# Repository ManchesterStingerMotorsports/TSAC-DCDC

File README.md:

# TSAC-DCDC
Low power HV-LV flyback converter to power the TSAC's internal safety circuitry.

Input voltage:

	Min: 35V to allow for single segment operation
	Max: 600V to allow for use across accumulator types

Estimated Output @ 12V with minimal ripple:

	6W continuous
	24W Peak

Webench design tool link for simulation and specs:
https://webench.ti.com/appinfo/webench/scripts/SDP.cgi?ID=1A791EA787B34855

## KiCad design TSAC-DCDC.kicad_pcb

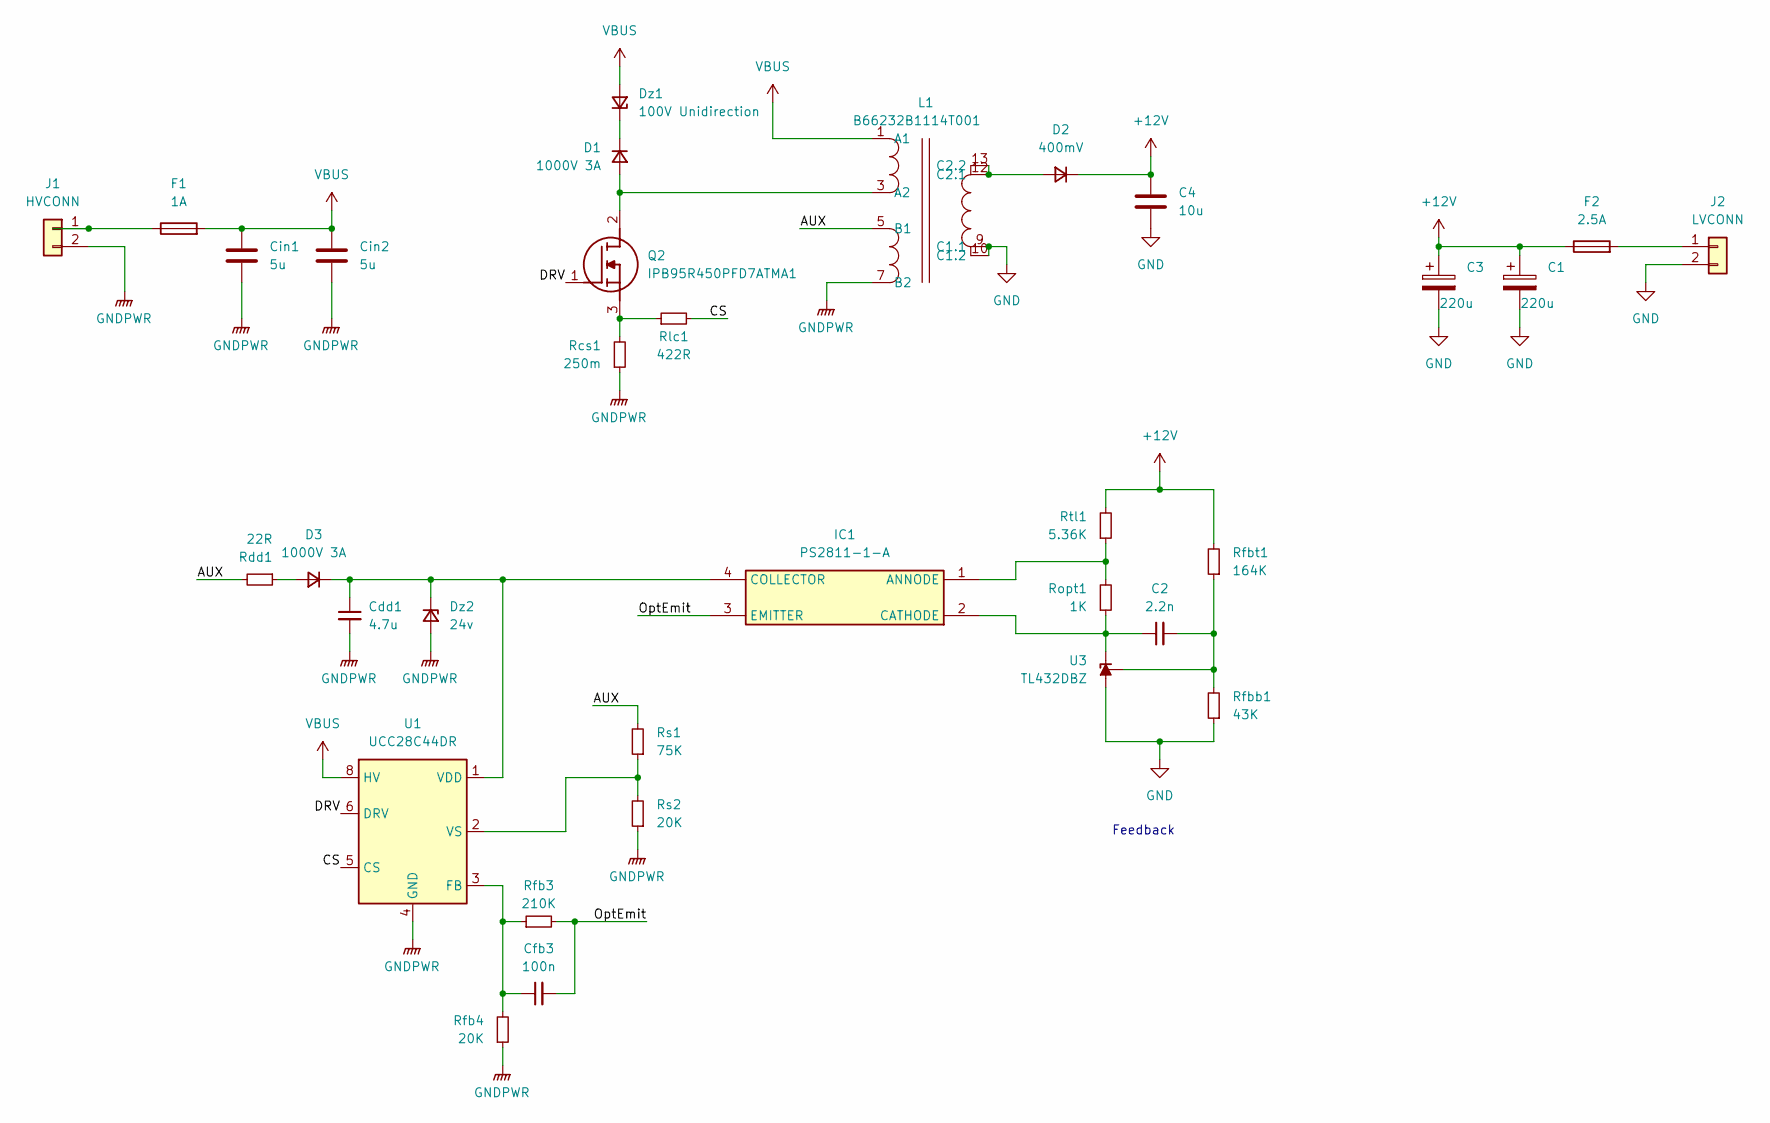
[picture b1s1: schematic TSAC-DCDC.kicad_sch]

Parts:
C1, C3: 220u; CP_Radial_D8.0mm_P3.50mm
C2: 2.2n; C_0603_1608Metric
C4: 10u; C_0603_1608Metric
Cdd1: 4.7u; C_0603_1608Metric
Cfb3: 100n; C_0603_1608Metric
Cin1, Cin2: 5u; ECWFG60505JA
D1, D3: 1000V 3A; D_SMB
D2: 400mV; TO-277A
Dz1: 100V Unidirection; D_SMC
Dz2: 24v; SOD-123-2
F1: 1A; FUSC13250X555N
F2: 2.5A; FUSC13250X555N
IC1: PS2811-1-A; SOIC127P700X210-4N; Mouser Part Number 551-PS2811-1-A
J1: HVCONN
J2: LVCONN
L1: B66232B1114T001; Mouser Part Number 871-B66232B1114T001
Q2: IPB95R450PFD7ATMA1; Mouser Part Number 726-IPB95R450PFD7ATM
Rcs1: 250m; R_0603_1608Metric
Rdd1: 22R; R_0603_1608Metric
Rfb3: 210K; R_0603_1608Metric
Rfb4: 20K; R_0603_1608Metric
Rfbb1: 43K; R_0603_1608Metric
Rfbt1: 164K; R_0603_1608Metric
Rlc1: 422R; R_0603_1608Metric
Ropt1: 1K; R_0603_1608Metric
Rs1: 75K; R_0603_1608Metric
Rs2: 20K; R_0603_1608Metric
Rtl1: 5.36K; R_0603_1608Metric
U1: UCC28C44DR; SOIC-8_3.9x4.9mm_P1.27mm
U3: TL432DBZ; SOT-23

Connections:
+12V: C1.1, C3.1, C4.1, D2.1 (K), F2.1, Rfbt1.2, Rtl1.2
/AUX: L1.5 (B1), Rdd1.2, Rs1.2
/CS: Rlc1.2, U1.5 (CS)
/DRV: Q2.1 (G), U1.6 (DRV)
/OptEmit: Cfb3.2, IC1.3 (EMITTER), Rfb3.2
GND: C1.2, C3.2, C4.2, J2.2, L1.9 (C1.1), L1.10 (C1.2), Rfbb1.1, U3.3 (A)
GNDPWR: Cdd1.2, Cin1.2, Cin2.2, Dz2.2 (A), J1.2, L1.7 (B2), Rcs1.1, Rfb4.1, Rs2.1, U1.4 (GND)
unnamed: D1.2 (A), L1.3 (A2), Q2.2 (D)
unnamed: D1.1 (K), Dz1.1 (K)
unnamed: D2.2 (A), L1.12 (C2.1), L1.13 (C2.2)
unnamed: D3.2 (A), Rdd1.1
unnamed: Cdd1.1, D3.1 (K), Dz2.1 (K), IC1.4 (COLLECTOR), U1.1 (VDD)
unnamed: IC1.1 (ANNODE), Ropt1.2, Rtl1.1
unnamed: C2.1, IC1.2 (CATHODE), Ropt1.1, U3.2 (K)
unnamed: F1.1, J1.1
unnamed: F2.2, J2.1
unnamed: Q2.3 (S), Rcs1.2, Rlc1.1
unnamed: Cfb3.1, Rfb3.1, Rfb4.2, U1.3 (FB)
unnamed: Rs1.1, Rs2.2, U1.2 (VS)
unnamed: C2.2, Rfbb1.2, Rfbt1.1, U3.1 (REF)
VBUS: Cin1.1, Cin2.1, Dz1.2 (A), F1.2, L1.1 (A1), U1.8 (HV)

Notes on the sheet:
Feedback

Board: 2 copper layers, 30 parts (0 on the bottom side), 19 nets, no tracks yet.

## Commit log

2025-11-05 Upload transformer spec sheet
2025-11-06 Rearrange sch for cleaner look.
2025-11-06 transformer pin update
2025-11-11 Add fuse to power input and output
2025-11-12 Add footprint to components
2025-11-30 First try of L-C inperfection
2025-12-03 Initial PCB layout
2025-12-08 Revert "Initial PCB layout"
    This reverts commit eb11546efb0268227655b0bea42a16ad7d7093c5.
